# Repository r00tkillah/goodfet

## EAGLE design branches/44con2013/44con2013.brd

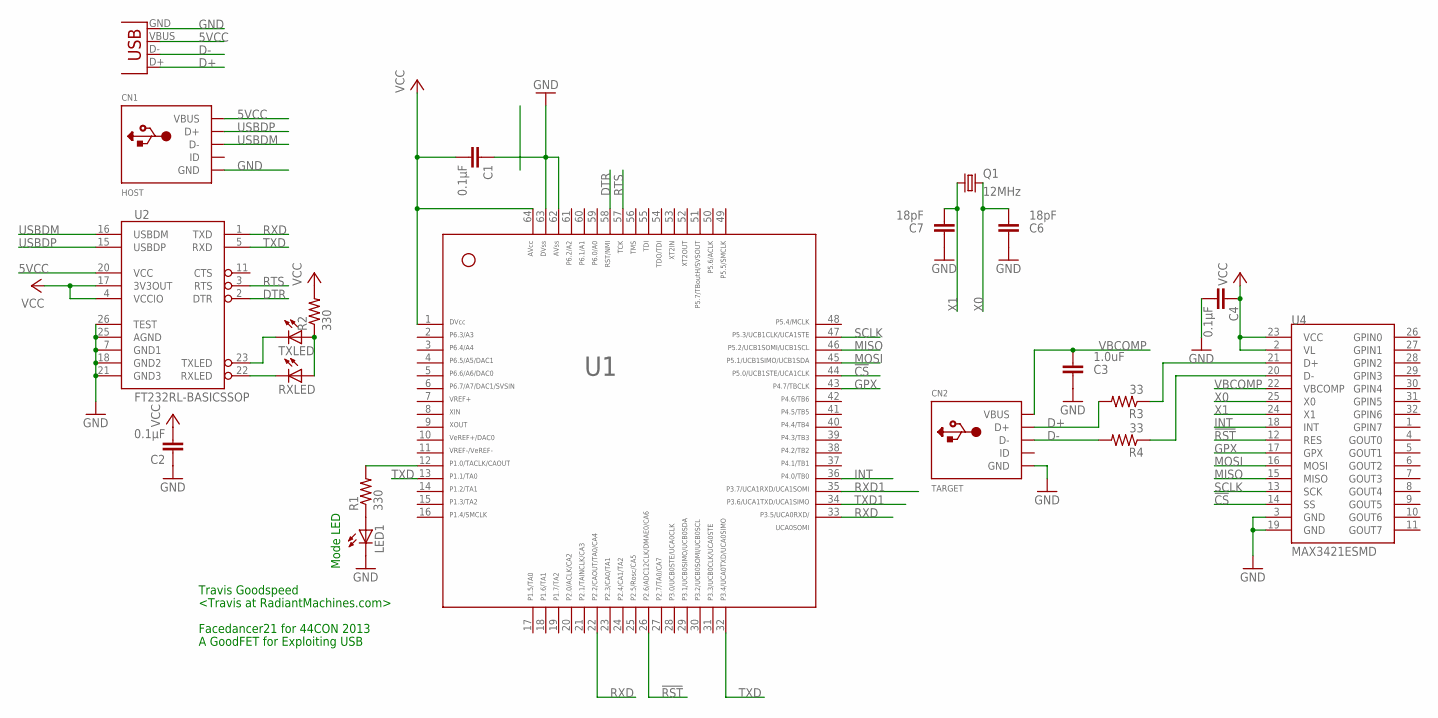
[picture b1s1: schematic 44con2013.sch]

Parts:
C1, C2, C4: 0.1µF; C0603
C3: 1.0uF; C0603
C6, C7: 18pF; C0603
CN1: HOST; USB-MINIB
CN2: TARGET; USB-MINIB
CN3: USB-A-S
LED1: LEDCHIP-LED0603; CHIP-LED0603
Q1: 12MHz; HC49UP
R1, R2: 330; R0603
R3, R4: 33; R0603
RXLED: LEDCHIP-LED0603; CHIP-LED0603
TXLED: LEDCHIP-LED0603; CHIP-LED0603
U1: F261X---PM64; PM/PAG64
U2: FT232RL-BASICSSOP; SSOP28DB
U4: MAX3421ESMD; TQFP32-5MM

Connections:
5VCC: CN1.VBUS, CN3.VBUS, U2.20 (VCC)
!CS: U1.44, U4.14 (SS)
!RST: U1.26, U4.12 (RES)
D+: CN2.D+, CN3.D+, R3.2
D-: CN2.D-, CN3.D-, R4.2
DMINUS: R4.1, U4.20 (D-)
DPLUS: R3.1, U4.21 (D+)
DTR: U1.58, U2.2 (DTR)
GND: C1.1, C2.1, C3.1, C4.2, C6.1, C7.1, CN1.GND, CN2.GND, CN3.GND, LED1.C, U1.62, U1.63, U2.7 (GND1), U2.18 (GND2), U2.21 (GND3), U2.25 (AGND), U2.26 (TEST), U4.3 (GND), U4.19 (GND)
GPX: U1.43, U4.17 (GPX)
INT: U1.36, U4.18 (INT)
MISO: U1.46, U4.15 (MISO)
MOSI: U1.45, U4.16 (MOSI)
unnamed: R1.2, U1.12
unnamed: LED1.A, R1.1
unnamed: RXLED.C, U2.22 (RXLED)
unnamed: TXLED.C, U2.23 (TXLED)
unnamed: R2.1, RXLED.A, TXLED.A
RTS: U1.57, U2.3 (RTS)
RXD: U1.22, U1.33, U2.1 (TXD)
RXD1: U1.35
SCLK: U1.47, U4.13 (SCK)
TXD: U1.13, U1.32, U2.5 (RXD)
TXD1: U1.34
USBDM: CN1.D-, U2.16 (USBDM)
USBDP: CN1.D+, U2.15 (USBDP)
VBCOMP: C3.2, CN2.VBUS, U4.22 (VBCOMP)
VCC: C1.2, C2.2, C4.1, R2.2, U1.1, U1.64, U2.4 (VCCIO), U2.17 (3V3OUT), U4.2 (VL), U4.23 (VCC)
X0: C6.2, Q1.2, U4.25 (X0)
X1: C7.2, Q1.1, U4.24 (X1)

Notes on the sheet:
Mode LED
Travis Goodspeed
<Travis at RadiantMachines.com>
Facedancer21 for 44CON 2013
A GoodFET for Exploiting USB

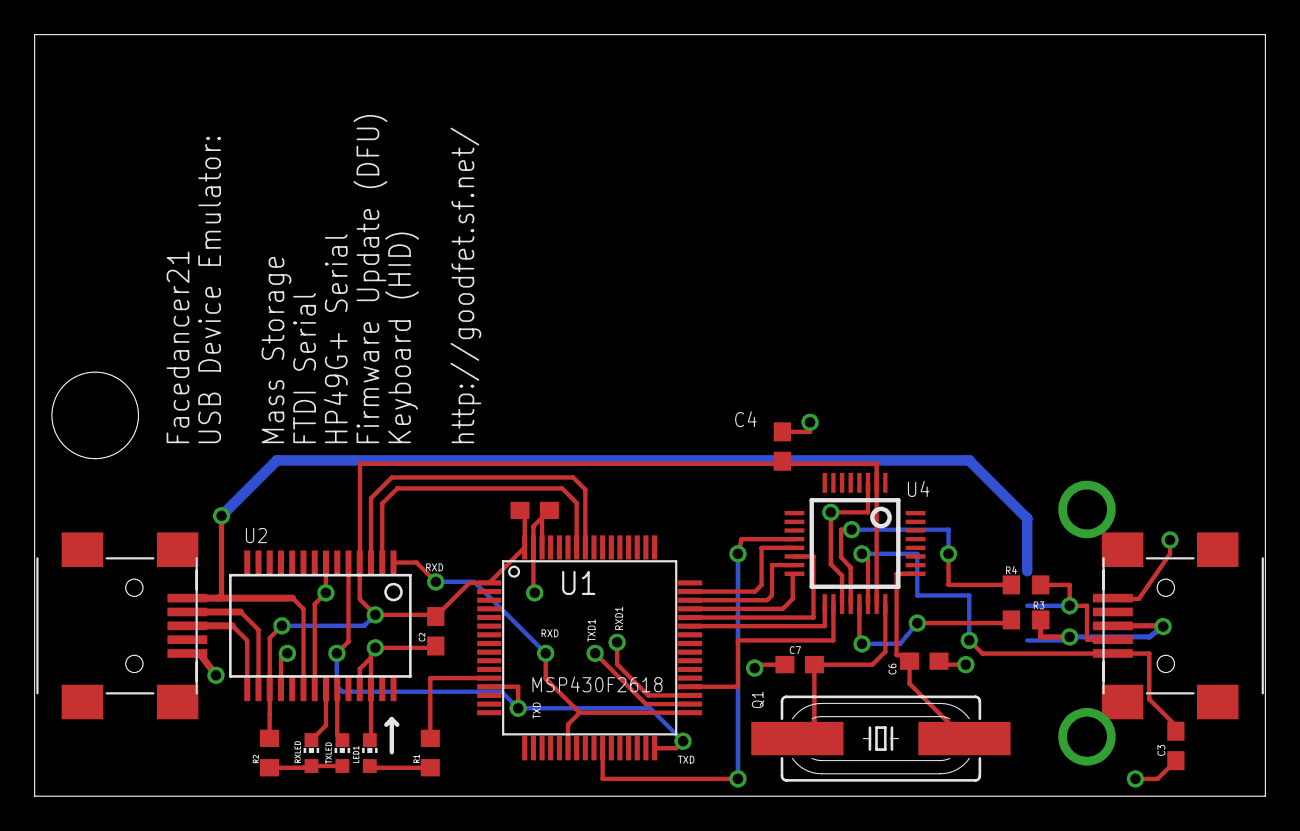
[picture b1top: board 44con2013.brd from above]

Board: 2 copper layers, 71.1 x 44.0 mm, 20 parts (1 on the bottom side), 28 nets.

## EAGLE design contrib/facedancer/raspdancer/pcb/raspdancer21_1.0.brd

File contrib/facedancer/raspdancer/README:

raspdancer11 is a variant of facedancer11 tailored for Raspberry Pi
raspdancer21 is a variant of facedancer21 tailored for Raspberry Pi

More info & contact:
====================
    Philippe Teuwen <phil teuwen.org>
    http://wiki.yobi.be/wiki/Raspdancer

Rationale:
==========
    Facedancer11/21 is a one-purpose version of the flexible GoodFET board.
It was well designed to move all the intelligence into the host controller,
not in the embedded uC. Therefore GoodFET part of the Facedancer11 design
can be seen as "just" a SPI over UART over USB bridge.
But Raspberry Pi has a native SPI support so let's make a dedicated version.
It's cheaper (you save FT232RL & MSP430F2618TPM).
It's faster (SPI communication with MAX3420E/MAX3421E gets boosted to 26MHz!).
It still uses the same GoodFETMAXUSB.py library.

Construction & components:
==========================
    See pcb/ for Eagle files.
Many thanks to Jean-Christophe Nicaise for the initial Eagle design.

Name   Package    Description
------ -------    -----------
U1     LQFP32-08  MAX3420E           (for facedancer11)
U1     TQPF32-5MM MAX3421E           (for facedancer21)
R1     0603       33R USB Serie Resistor
R2     0603       33R USB Serie Resistor
C1     0603       1.0µF Capacitor
C2     0603       0.1µF Decoupling Capacitor
C3     0603       18pF Capacitor
C4     0603       18pF Capacitor
C5     0603       1.0µF Capacitor
Q1     5x3.2      12MHz SMD Crystal, 18pF      (see note)
USB    USB Mini   Receptacle e.g. UX60-MB-5ST
J_RASP 2x13       Receptacle, 2.54mm, 26way    (see note)

Differences with original Facedancer11/21 (besides removal of GoodFET parts):
* smaller crystal package
* 2x13 connector towards RPi, e.g. a SAMTEC BCS-113-L-D-TE, or even a smaller
  one as 2x6 is enough, but then be the sure to plug the board correctly
  into the larger RPi connector!
* pads on the USB line, in case you want to solder directly a USB cable on it.
* Jumper to allow powering the RPi over this USB but beware:
  You're fuzzing the one which is powering you,
  don't cry if you experience power losses...
  RPi polyfuse is bypassed but power from a *real* USB port should be fine.
* Jumper to allow connecting INT to GPIO24 in case it gets used in the future
* Jumper to allow connecting GPX to GPIO23 in case it gets used in the future

Software:
=========
    Things have been done to be able to reuse the MAXUSB python libraries
written for facedancer11. All you need is to replace the original GoodFET.py
by the version provided here. It relies on SPI and GPIO libraries, see below.
Code has to be run as root or user with enough rights on SPI & GPIO.

Activating SPI on Raspberry PI
------------------------------
Edit /etc/modprobe.d/raspi-blacklist.conf and comment this line then reboot:
 #blacklist spi-bcm2708

Python SPI library for Raspberry Pi
-----------------------------------
We're using this one:
https://github.com/lthiery/SPI-Py (tested with commit b2c7854c, 2013-04-15)
 wget https://raw.github.com/lthiery/SPI-Py/master/spi.c
 wget https://raw.github.com/lthiery/SPI-Py/master/setup.py
 apt-get install python2.7-dev
 python setup.py build
 Result spi.so is in build/lib.linux-armv6l-2.7/, to be dropped in python path

Python GPIO library for Raspberry Pi
------------------------------------
We're using this one:
https://code.google.com/p/raspberry-gpio-python/
We tested the version v0.4.1a-1 which is pre-installed on Raspbian

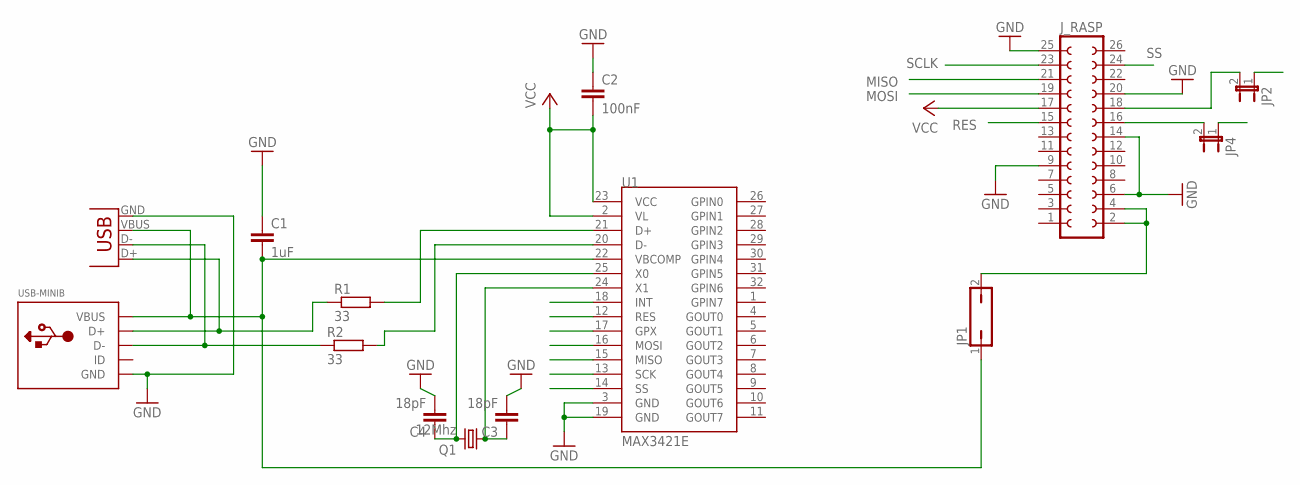
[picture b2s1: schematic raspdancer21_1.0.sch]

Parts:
C1: 1uF; C1206
C2: 100nF; C1206
C3, C4: 18pF; C1206
JP1: JP1Q; JP1
JP2, JP4: JUMPER-2-OLDSMD-NO; SJ_2S-NO
JP5: USB-A-S
J_RASP: FE13-2
Q1: 12Mhz; CTS406
R1, R2: 33; R1206
U1: MAX3421E; TQFP32-5MM
USB-MINIB: USBMINIB; USB-MINIB

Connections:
D+: R1.2, U1.21 (D+)
D+2: JP5.D+, R1.1, USB-MINIB.D+; also elsewhere on the board
D-: R2.2, U1.20 (D-)
D-2: JP5.D-, R2.1, USB-MINIB.D-; also elsewhere on the board
GND: C1.1, C2.1, C3.2, C4.2, JP5.GND, J_RASP.6, J_RASP.9, J_RASP.14, J_RASP.20, J_RASP.25, U1.3 (GND), U1.19 (GND), USB-MINIB.GND; also elsewhere on the board
GPX: JP4.1, U1.17 (GPX)
GPX2: JP4.2, J_RASP.16
INT: JP2.1, U1.18 (INT)
INT2: JP2.2, J_RASP.18
IX: C4.1, Q1.3 (2), U1.25 (X0)
MISO: J_RASP.21, U1.15 (MISO)
MOSI: J_RASP.19, U1.16 (MOSI)
RES: J_RASP.15, U1.12 (RES)
SCLK: J_RASP.23, U1.13 (SCK)
SS: J_RASP.24, U1.14 (SS)
VBUS: C1.2, JP1.1, JP5.VBUS, U1.22 (VBCOMP), USB-MINIB.VBUS; also elsewhere on the board
VBUS2: JP1.2, J_RASP.2, J_RASP.4
VCC: C2.2, J_RASP.17, U1.2 (VL), U1.23 (VCC)
XO: C3.1, Q1.1, U1.24 (X1)

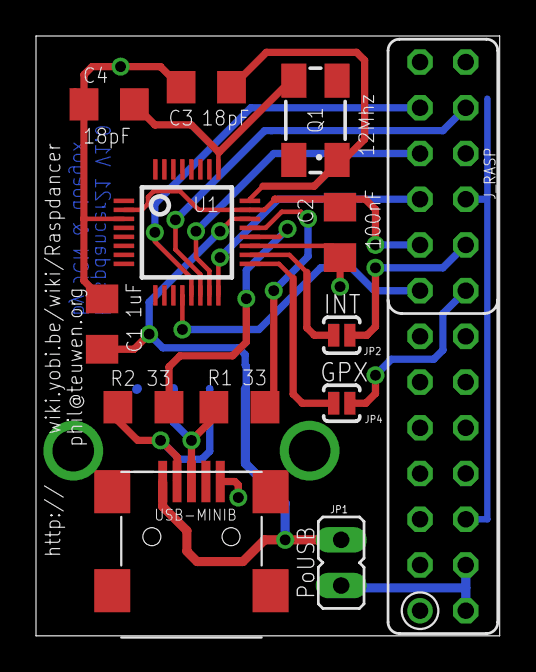
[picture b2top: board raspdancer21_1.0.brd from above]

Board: 2 copper layers, 25.8 x 33.3 mm, 14 parts (1 on the bottom side), 19 nets.

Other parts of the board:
USB-A: USB-A-S

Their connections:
D+2: USB-A.D+; also elsewhere on the board
D-2: USB-A.D-; also elsewhere on the board
GND: USB-A.GND; also elsewhere on the board
VBUS: USB-A.VBUS; also elsewhere on the board

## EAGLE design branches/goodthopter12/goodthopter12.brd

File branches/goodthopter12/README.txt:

GoodThopter12 CAN Adapter

IMPORTANT - "PLUG BUG FIX"

It turns out OBD2 cables have a variety of pinouts, specifically at
the DB9 connector. The two most popular for CAN that I have seen are
CANH on pins (7,3) and CANL on (5,2) - to accommodate both pinouts
GoodThopter12 includes resistors (R5-R8) that are 0 OHM and act as
jumpers to connect the pins that correlate to your cable.

EX: The Sparkfun cable supports CANH on pin 3 and CANL on pin 5 so you
would connect resistors R7 and R6 to support your cable.

--

The GoodThopter is the sexy GoodFET CAN Adapter, whose purpose is to
route CAN connection from an automobile or ECU into a laptop
leveraging the maturing GoodFET firmware and project.  Care has been
taken to keep the design easy to solder and the code easy to modify.

If you like this project, the following will humbly accept beer
donations:

Andrew Righter, GoodThopter Project Lead
Travis Goodspeed, Circuit Preacher

CAN Hacking Inspired By:
-Late night drinking in the Midwest with Atlas and Cutaway.
-Late night drinking in Downtown Metropolitan Etna with Sergey Bratus
 singing ``Hop on the Magic School Bus!''
-Late night cramming in Philly to meet an absurd deadline that's
 demonstrably Andrew's fault, but without which you wouldn't have a
 neighborly GoodThopter.

If you have any questions/comments:

Andrew Righter <andrew@215LAB.com>

bugs/development:
http://goodfet.sf.net/
goodfet-devel@lists.sourceforge.net

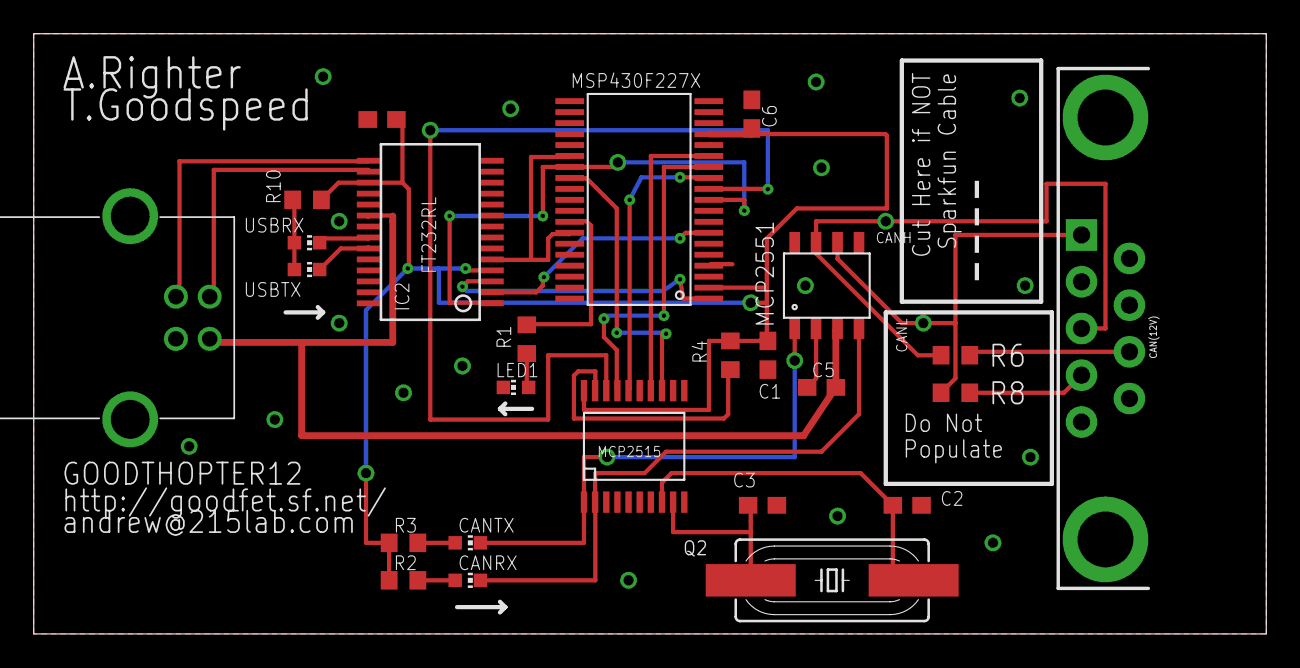
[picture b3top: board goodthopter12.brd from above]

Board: 2 copper layers, 73.0 x 35.6 mm, 25 parts (0 on the bottom side), 30 nets.

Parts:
292304-2: MINI-USB_4P-292304-2; 85-32004-10X
C1, C4: 0.1µF; C0603
C2, C3: 15pF; C0603
C5, C6: 0.1uF; C0603
CAN(12V): DB9_MALE
CANRX: CHIP-LED0603
CANTX: CHIP-LED0603
IC1: F22X4---DA38; DA38
IC2: FT232RL-BASICSSOP; SSOP28DB
LED1: CHIP-LED0603
Q2: 20MHz; HC49UP
R1, R2, R3, R10: 330; R0603
R4: 10k; R0603
R6, R8: 0; R0603
U$1: MCP2515; TSSOP20
U$2: MCP2551; SOIC-8
USBRX: CHIP-LED0603
USBTX: CHIP-LED0603

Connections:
!CS: IC1.11, U$1.18
!INT: IC1.27, U$1.13
CANH: CAN(12V).3, R6.2, U$2.CANH
CANL: CAN(12V).5, R8.1, U$2.CANL
DTR: IC1.7, IC2.2
GND: 292304-2.4, C1.1, C2.1, C3.1, C4.1, C5.1, C6.1, IC1.4, IC1.15, IC2.7, IC2.18, IC2.21, IC2.25, IC2.26, LED1.C, U$1.10, U$2.RS, U$2.VSS
MISO: IC1.13, U$1.17
MOSI: IC1.12, U$1.16
unnamed: CANRX.A, R2.2
unnamed: CANTX.A, R3.2
unnamed: CAN(12V).2, R8.2
unnamed: R4.2, U$1.19
unnamed: IC2.22, USBRX.C
unnamed: IC2.23, USBTX.C
unnamed: R10.1, USBRX.A, USBTX.A
unnamed: IC1.31, R1.2
unnamed: LED1.A, R1.1
unnamed: CAN(12V).7, R6.1
OSC1: C3.2, Q2.1, U$1.9
OSC2: C2.2, Q2.2, U$1.8
RTS: IC1.1, IC2.3
RXCAN: CANRX.C, U$1.2, U$2.RXD
RXD: IC1.10, IC1.26, IC2.1
SCK: IC1.14, U$1.14
TXCAN: CANTX.C, U$1.1, U$2.TXD
TXD: IC1.25, IC1.32, IC2.5
USBDM: 292304-2.2, IC2.16
USBDP: 292304-2.3, IC2.15
VCC: C1.2, C4.2, C6.2, IC1.2, IC1.16, IC2.4, IC2.17, R2.1, R3.1, R4.1, R10.2, U$1.20
VCC5V: 292304-2.1, C5.2, IC2.20, U$2.VDD

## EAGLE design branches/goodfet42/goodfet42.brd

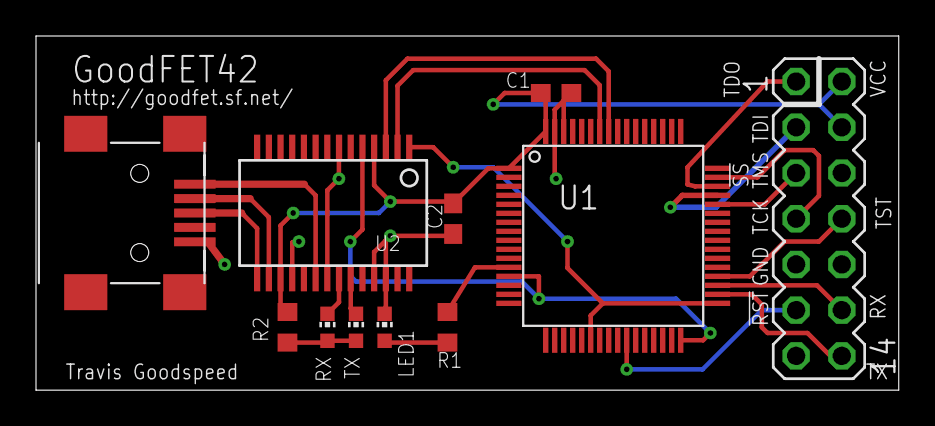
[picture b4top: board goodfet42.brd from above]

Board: 2 copper layers, 47.9 x 19.7 mm, 11 parts (0 on the bottom side), 22 nets.

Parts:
C1, C2: 0.1µF; C0603
CN1: USB-MINIB
JTAG: MA07-2
LED1: CHIP-LED0603
R1, R2: 330; R0603
RX: CHIP-LED0603
TX: CHIP-LED0603
U1: MSP430F2618TPM; PM/PAG64
U2: FT232RL; SSOP28DB

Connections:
5VCC: CN1.VBUS, U2.20
DTR: U1.58, U2.2
GND: C1.1, C2.1, CN1.GND, JTAG.9, LED1.C, U1.62, U1.63, U2.7, U2.18, U2.21, U2.25, U2.26
unnamed: R1.2, U1.12
unnamed: LED1.A, R1.1
unnamed: RX.C, U2.22
unnamed: TX.C, U2.23
unnamed: R2.1, RX.A, TX.A
RST: JTAG.11, U1.26
RTS: U1.57, U2.3
RXD: U1.22, U1.33, U2.1
RXD1: JTAG.12, U1.35
TCK: JTAG.7, U1.47
TDI: JTAG.3, U1.45
TDO: JTAG.1, U1.46
TEST: JTAG.8, U1.36
TMS: JTAG.5, U1.44
TXD: U1.13, U1.32, U2.5
TXD1: JTAG.14, U1.34
USBDM: CN1.D-, U2.16
USBDP: CN1.D+, U2.15
VCC: C1.2, C2.2, JTAG.2, JTAG.4, R2.2, U1.1, U1.64, U2.4, U2.17

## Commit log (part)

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2012-10-01 Minor cleanup.
2012-10-07 Added godfet.maxusbdfu for USD Device Firmware Update emulation with the Facedancer.
2012-10-10 Updated GoodThopter11 Board
2012-10-22 Moved via away from IC in GT11.
2012-10-25 GoodFET42 layout. Might not be final.
2012-10-26 link to example Digi-Key order for Facedancer11 parts
2012-10-30 New code for setting the rate. Tested at 125kHz.
2012-10-30 goodfet.mcpcan's sniff verb now supports setting a data rate.
2012-10-30 Allowing a rate of 83.3
2012-10-31 Created intelligent sniffer (isniff) to help decode CAN messages
2012-11-03 Added GT11, fixed BOM of GT10.
2012-11-03 MCP CAN doccos.
2012-11-03 GT11 firmware.
2012-11-03 Typo.
2012-11-04 Rebuild CAM files for GF42.
2012-11-05 Added win32 instructions.
2012-11-06 Tiny silkscreen placement change in GF42.
2012-11-07 gflpc1343 parts selection, paste clearance
2012-11-07 add Linked List files i forgot
2012-11-09 JTAGARM7 is back up and running, folks! Tested Halt/Release, Get/Set Registers, Read/Write Memory.
2012-11-11 and the peek does the size better (without specifying an end, it was giving odd results)
2012-11-12 updates to use the ARMresettarget() for "goodfet.arm7 reset" which uses the nRST pin
2012-11-15 ARMread/writeStream() functions enabled, allowing the reading/writing of byte-aligned bytes, not just 32-bit word-aligned numbers
2012-11-15 yield instead of returning a list of values for ARMreadChunk. also, check out ARMreadStream and ARMwriteStream functions! way handy for dealing with strings and when you want to be byte-aligned, not 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
2012-11-16 Socks with hops.
2012-11-19 HID patches and a bit of host fingerprinting from Kenny at Romhat.
2012-11-22 goodfet.maxusbmass now has increased to 128 blocks per transfer, fixed failure codes.
2012-11-22 Updated GoodThopter11 HTML page to explain OBD2 cable choice.
2012-11-23 Facedancer20 gerbers.
2012-11-24 Added APP number to GoodFETSPI.
2012-11-25 Beginnings of support for Zigduino. AVR code is really out of shape.
2012-11-30 Status page update. Still needs a rewrite.
2012-12-04 OpenSCAD models for Makerbot-able GoodFET casings.
2012-12-05 OpenSCAD models for the GoodThopter. Parametrics are cool.
2012-12-12 Removed outdated installation instructions.
2012-12-14 Added basic firmware and client support for the zigduino/atmel128rfa1. It can now rx and tx packets.
2013-01-04 Fixed GF42 links. Boards should arrive soon.
2013-01-04 Link to second Facedancer article. Third one ought to be up before too damned much time has passed.
2013-01-04 working on goodfet.bsl improvements to --fromweb and trying to preserve info flash
2013-01-06 This seems to fix the undesired chip erase when doing --dumpinfo
2013-01-15 upload goodfet.mcpcanCommunication.py
2013-01-16 updated DataManage.py with .pcap writing capabilities
2013-01-16 Renaming FD21 files.
2013-01-16 updated DataManage.py
2013-01-17 FD20 erratum, orders.
2013-01-17 FD21 docs.
2013-01-17 FD20 image.
2013-01-17 Added erratum note to FD20 schematic.
2013-01-17 uploaded some data files and reviced Data code
2013-01-20 Two typos in the website.
2013-01-20 Cleaned up tab inconsistency in usb_max.py.
2013-01-22 Updates to GoodFETMCPCANCommunication.py. Pared down SPI transmission in sniff, speeding it up, and added filtering options to filter for packets with specified standard IDs
2013-01-22 updated working GUI file: mainDisplay.py. This should now have working sniff with filtering ability. You can also run a SQL query and save to csv file
2013-01-22 Changes to GoodFETMCPCANCommunication.py. Added file management capabilities back. fixed error
2013-01-23 First draft of GoodFET32.
2013-01-24 testing commit ability
2013-01-24 jtagarm7 interface improvements, including at91x40
2013-01-24 jtagarm7 more obligatory stupid bug fixes, doh!
2013-01-25 added fast packet sniffing option -x. doubles RX speed but could easily result in duplicate packets. use with caution-- should be set to respond to interrupt from MCP
2013-01-25 jtagarm7 at91x40 ecdump updates and bugfixes
2013-01-25 new test file for sweeping
2013-01-26 small changes to upload method in DataManage
2013-01-27 minor updates to spit-testing function
2013-01-29 added parsing abilities to sniff as well as improvements to the simpleGUI
2013-01-29 functionality changes to mainDisplay. added settings, writing section, reorganized and cleaned filtering and sniffing
2013-01-30 GUI updated to include writing and experiment capabilities. Updated spit capabilities to allow for user to set the packet they wish to send
2013-01-30 bug fixes in mainDisplay and spit method of GoodFETMCPCANCommunication
2013-01-30 fixed filtering issue on mainDisplay.py
2013-02-01 spit changes to allow user to run from commandline
2013-02-01 built a rtr sweep to check all ids on the car
2013-02-01 changes to the rtr sweep method in communication file
2013-02-01 changes to communication and sweep methods
2013-02-02 changed the preset values for the experiments
2013-02-03 building arbID information secion in mainDisplay file
2013-02-05 update to threading of sniff on mainDisplay as well as added option to sniff in communication file
2013-02-05 small changes to display
2013-02-05 oops. fix for GoodFETARM9
2013-02-05 jtagarm9 - will get things settled eventually
2013-02-05 changes to get the threading working for sniff in mainDisplay. removed bugs
2013-02-06 changes to the hyperlink commands to allow for arbID link binding
2013-02-06 DataManage to update to Wireshark from SQL
2013-02-06 changes to allow for deltaT of each packet to work. debugged and displaying nicely
2013-02-07 jtagarm: jtag_trans_many tested and working. this will allow us to abstract out all versions of ARM debug interface including ARM7TDMI (existing in gf already), ARM9TDMI, ARM11, ADIv4 and ADIv5 (and 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
2013-02-08 improved ecdump... actually goes back and rereads sections that have failed. failures were causing breaks in segments.
2013-02-11 changes to the display of data
2013-02-11 Somehow the manual.html page wasn't committed to subversion. Here it is.
2013-02-11 More broken images.
2013-02-12 changes to the GUI to allow for better loading and writing as well as tested our FordExperiments stuff
2013-02-12 changes to debug the spit/write code and my ford experiments
2013-02-12 Fix missing links for apps and clients
2013-02-13 minor bug fix on parsing experiments data
2013-02-13 GoodFET32 heading off to the factory.
2013-02-13 updated features for two different types of sniffing. fixed and scrolling. This can be changed on the gui
2013-02-13 added an display for the time difference between every successive packet read off the chip
2013-02-13 Facedancer21 locked in. Ordering soon.
2013-02-14 added packet fuzzing
2013-02-14 Fixed USB host bugs.
2013-02-15 Added the option to automatically re-inject packets that we have fuzzed and injected before. Also added threading to the experiments so that you can set up for the next one while one is running
2013-02-15 generalized the generation fuzzer to allow you to choose which ids you want to randomly inject also
2013-02-18 I2C master app and client. Impressively ugly. Might work occasionally.
2013-02-18 added Comments to a lot of the methods
2013-02-19 updated some new experiment methods. you can now fuzz on all ids randomly as well as do a listen response method
2013-02-19 Added a lot of comments to fully describe alot of the methods we have created.
2013-02-20 added filtering on data bytes; use -db0 and -db1 flag on sniff
2013-02-20 added flexible packet sending function, multiPacketSpit
2013-02-20 debugged my attempt to fake the VIN
2013-02-20 i2c.c fixes including: - timing cleanup - release bus after transactions so other masters may take the bus
2013-02-21 updated the GUI to be more usable. added some error checking, warning dialogs
2013-02-22 added comments, rearranged code to be more readable
2013-02-24 added car module section
2013-02-24 build out demonstration gui
2013-02-24 debugging changes
2013-02-25 Completed packet information display
2013-02-25 debugged speedometer hack, added RPM hack
2013-02-26 added demonstration code
2013-02-26 building demonstration frame
2013-02-26 updates to demonstration display
2013-02-27 added demonstration features
2013-02-27 added information about ids
2013-02-28 beethoven hack
2013-02-28 added diagnostic method
2013-02-28 debugged the demonstration methods
2013-03-01 changes to dbugging
2013-03-06 Website update that was accidentally done from the old URL.
2013-03-13 Developer URL.
2013-03-29 Bug fixes and new features added to zigduino firmware and client. New features include: - auto checksum support added - auto checksum can be enabled and diabled - support for radio's extended operati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
2013-03-30 Releasing GoodThopter12 (requires review) fixing PlugBug, supports multiple OBD2 cables.
2013-04-07 Renamed some LEDs. Closer to ordering GoodThopter12 boards.
2013-04-07 Updated GoodThopter12 HTML page, not linked to menu NEEDS to be pushed.
2013-04-07 Final fixes for GT12. Gerbers coming in the next commit.
2013-04-16 Applying some good recommendations from Bruce Barnett - Add --dumpinfo to --help output - Display usage information before considering board definition - Look at alternatives to curl if it is not ava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
2013-04-17 Moving older bootstrap loader aside in preparation for merging in a newer branched version.
2013-04-17 Documentation updates to reflect changes in --fromweb functionality.
2013-04-24 Provide a little bit more user feedback when serInit is stalling out.
2013-05-04 FD21 and assembled board ordering info.
2013-05-05 GF32 support in the new goodfet.bsl.
2013-05-06 raspdancer11 board: more room around IC and other small changes
2013-05-07 Add raspdancer21 sch & brd
2013-05-09 raspdancer21: fix silkscreen
2013-05-12 raspdancer: larger wires & vias & some tunings
2013-06-04 Added initial support for board=apimote2
2013-06-14 new maxusb library
2013-06-15 Python 3.2 for the rewritten Facedancer clients.
2013-06-16 added documentation
2013-06-19 removing an unecessary failed experiment
2013-06-19 handle scsi mode sense to get umass working under linux
2013-06-19 add (hopefully) support for vendors
2013-06-19 correct ftdi vendor info
2013-06-19 fix endianness in device descriptor
2013-06-21 updating SVN link in tutorial
2013-06-21 removed MySQLdb package necessity
2013-07-13 Fixed merge conflict noticed by @Marsmensch.
2013-07-13 GF32 photo.
2013-07-14 TOAD: CPLD decoupling caps, rearranged headers to expose JTAG, etc.
2013-07-18 TOAD: comparator voltage dividers
2013-08-06 No Such Badge
2013-08-14 Added ordering links for GF42 and FD21 to the FAQ.
2013-08-30 bug fixes from Adam Stasiak <palesius@gmail.com>
2013-08-31 Facedancer support for emulating USB LCD devices.
2013-09-15 44con badge.
2013-09-15 Indentation fixes.
    * stop using TAB's for indentation, some (arguably silly) editors use
    4-space TAB's in Python mode
    * fixed inconsistent indentations
2013-09-15 Add missing newline in trace.
    This error somehow demonstrate the usefulness of "print >>sys.stderr" :)
2013-09-15 Add traces in some conditional blocs that did not have one.
    Easier to make sure of the exact code path used.
2013-09-16 Patches I2C client to dump eeproms + add bus scanning capability (untested yet!!)
2013-09-25 Bad link in I2C website.
2013-09-26 Do not hardcode app_num 0 in GoodFETMonitorApp.
2013-09-26 Factorize serial port opening in GoodFETSerialPort().
2013-10-04 H2HC 2013 Badge, based on gflpc1343
2013-10-26 TOAD layout that I forgot to commit previously
2013-10-27 Preliminary BOM. Not yet tested working.
2013-11-05 No changes to the layout have been made in this file. I just opened the manually edited file from the previous checkin, then saved it without making any changes. The garbage collector removed the unu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
2014-01-03 FD21 mistakenly mentioned errata. Fix from Protagonist.
2014-01-14 change hardcoded port name to use GOODFET env var or default it to /dev/ttyUSB0
2014-02-06 Add support for Zen-Sys ASICs firmware manipulation
2014-03-04 GoodThopter12.
2014-03-16 Fixed URL in the download page.
2014-04-21 It doesn't exactly work. Fixed one error to find another
    $ ./facedancer-skel.py
    Facedancer reset
    GoodFET monitor initialized
    MAXUSB initialized
    MAXUSB enabled
    MAXUSB revision 19
2014-04-25 splat with A
2014-05-17 tested progress from exploit workshop, then untested stuff
    a stupid git does not commit to git enough
2014-05-23 make things a little neater

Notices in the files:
parts and their libraries:
SparkFun-DigitalIC: Licensing: CC v3.0 Share-Alike You are welcome to use this library for commercial purposes.
